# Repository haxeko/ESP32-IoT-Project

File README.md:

# ESP32-IoT-Project
Make ESP32 IoT Device

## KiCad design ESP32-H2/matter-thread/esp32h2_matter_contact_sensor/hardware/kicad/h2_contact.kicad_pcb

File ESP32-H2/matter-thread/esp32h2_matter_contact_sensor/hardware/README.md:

# h2-contact v1.0: PCB cảm biến cửa ESP32-H2 Matter over Thread

Bo mạch riêng cho firmware [`../`](../README.md): module **ESP32-H2-MINI-1-N4**, cấp nguồn và nạp qua **USB-C**, domino 2 chân cho **reed switch** (công tắc từ). Chân khớp với giá trị mặc định của firmware nên chỉ cần build và nạp, không phải đổi `menuconfig` (riêng LED phải bật, xem mục **Firmware**).

| | |
|---|---|
| Kích thước | 26 × 46 mm, bo góc R1,5; 2 lớp; FR-4 1,6 mm |
| Lắp ráp | toàn bộ SMD ở **mặt trên** (lắp 1 mặt); J2 (domino, xuyên lỗ) hàn tay |
| Luật thiết kế | dây ≥ 0,2 mm, khoảng cách ≥ 0,2 mm, via 0,6/0,3 mm, đồng cách mép bo ≥ 0,3 mm (trong khả năng tiêu chuẩn của JLCPCB) |
| Lỗ bắt vít | 2 × M2 (H1, H2) |
| Nguồn | USB-C 5 V → PTC 0,5 A → TVS SMF5.0A → AP2112K-3.3 (600 mA) |
| Nạp, log | USB-C (USB Serial/JTAG của ESP32-H2, GPIO26/27), USBLC6-2SC6 chống ESD; pad UART0 ở mặt dưới |

## Thư mục

| Đường dẫn | Nội dung |
|---|---|
| `kicad/` | Project KiCad 7 (`h2_contact.kicad_pro`): sơ đồ A3, PCB đã đi dây, symbol `ESP32-H2-MINI-1` và footprint module (thư viện Espressif) |
| `fab/h2_contact_gerbers.zip` | Gerber X2 + Excellon (lỗ oval của USB-C dạng G85) + drill map + job file: **file upload cho xưởng** |
| `fab/gerbers/` | các file trong zip, để xem từng lớp |
| `fab/h2_contact-BOM.csv` | BOM đầy đủ (có ghi chú linh kiện), kể cả J2 |
| `fab/h2_contact-BOM-JLCPCB.csv`, `fab/h2_contact-CPL-JLCPCB.csv` | BOM và file toạ độ (CPL) theo cột của JLCPCB, không có J2 (hàn tay) |
| `fab/h2_contact-pos.csv` | file toạ độ gốc của KiCad (mm, cả hai mặt) |
| `fab/h2_contact_schematic.pdf` | sơ đồ nguyên lý |
| `docs/images/` | ảnh mặt trên, lớp đồng trên, lớp đồng dưới (nhìn từ dưới) |
| `tools/gen/` | script dựng lại toàn bộ (mục **Dựng lại**) |

## Sơ đồ khối và gán chân

| Khối | Linh kiện | Chân ESP32-H2 (pad module) | Firmware (`menuconfig`) |
|---|---|---|---|
| Reed switch | J2 (REED, GND) → R7 10k kéo lên 3V3 ở phía domino → R8 1k → GPIO4; C7 100 nF xuống GND; D2 ESD 3,3 V | GPIO4 (18) | `CONTACT_SENSOR_GPIO=4`, `CONTACT_ACTIVE_LOW=y` (mặc định) |
| Nút BOOT / factory reset | SW2 xuống GND, R4 10k kéo lên | GPIO9 (23) | `FACTORY_RESET_GPIO=9`, giữ 6 s (mặc định) |
| Nút RESET | SW1 xuống GND; EN: R3 10k + C6 1 µF | EN (8) | — |
| Strapping | R5 10k kéo GPIO8 lên: cần cho chế độ nạp (GPIO8 = 1, GPIO9 = 0) | GPIO8 (22) | — |
| LED trạng thái | GPIO5 → R6 1k → LED xanh lá → GND (sáng mức cao) | GPIO5 (19) | `STATUS_LED_ENABLE=y`, `STATUS_LED_GPIO=5`, `STATUS_LED_ACTIVE_HIGH=y` |
| USB | J1 D−/D+ → U3 USBLC6-2SC6 → R10/R9 22 Ω → GPIO26/GPIO27 | 26, 27 | USB Serial/JTAG (nạp, log) |
| UART0 | pad TX0/RX0 (mặt dưới) | TXD0 (31), RXD0 (30) | log UART0 (mặc định của ESP-IDF) |
| Nguồn module | C4 10 µF + C5 100 nF sát chân 3V3 | 3V3 (3) | — |

- **VBAT (chân 15)** để trống: datasheet ESP32-H2-MINI-1 v1.6 (bảng 3, hình 7) ghi chân này nối sẵn với 3V3 bên trong module qua R2 0 Ω.
- Chân NC của module (4, 7, 17, 28, 29, 32–35) và GPIO không dùng (IO0–IO3, IO10–IO14, IO22, IO25) để trống. IO25 là chân strapping JTAG, để trống là mặc định.
- Mọi pad GND của module, kể cả EPAD, nối vào mặt GND phía trên; 2 mặt GND nối nhau bằng 70 via khâu và via của linh kiện.

## Nối reed switch

Domino J2, nhìn từ mép dưới của bo: trái **REED** (pad vuông), phải **GND**. Đưa 2 dây của reed switch vào hai chân, không phân cực.

- Dùng loại tiếp điểm **đóng khi nam châm ở gần** (cửa đóng → mạch kín). Đó là reed switch thường hở (NO) và cũng là kiểu cảm biến cửa có dây phổ biến (MC-38 và tương tự, thường được bán với tên "NC" theo cách gọi của ngành báo động: mạch kín khi cửa đóng). Firmware mặc định hiểu: **mạch kín = cửa đóng**. Loại ngược lại thì tắt `CONTACT_ACTIVE_LOW`.
- Dây dài được: R7 10k kéo lên ở phía domino cho dòng khoảng 0,3 mA qua tiếp điểm khi đóng; R8 1k + C7 100 nF lọc nhiễu; D2 chặn ESD. Firmware còn lọc dội 50 ms.
- Không nối nguồn ngoài vào J2.

## Firmware

Dùng nguyên firmware ở thư mục cha. Build như README firmware; muốn dùng LED trên bo thì bật một lựa chọn:

```bash
idf.py menuconfig   # Status LED → Status LED on a GPIO = y (GPIO5 và "LED lights when HIGH" đã đúng mặc định)
```

Nạp qua cổng USB-C của bo (Linux `/dev/ttyACM0`):

```bash
idf.py -p /dev/ttyACM0 flash monitor
```

Nếu USB không nhận (firmware lỗi): giữ **BOOT**, bấm **RESET**, nhả BOOT → chế độ nạp ROM. Sau khi firmware chạy, giữ **BOOT 6 giây** = factory reset Matter (cảnh báo: giữ BOOT **trong lúc cắm USB/reset** là vào chế độ nạp, không phải factory reset).

## Đặt làm ở JLCPCB (hoặc xưởng khác)

1. **PCB:** upload `fab/h2_contact_gerbers.zip`. 2 lớp, 1,6 mm, tuỳ chọn mặc định. Kích thước xưởng đọc được: 26 × 46 mm.
2. **Lắp ráp (PCBA):** chọn lắp **mặt trên** (Top). Upload `fab/h2_contact-BOM-JLCPCB.csv` và `fab/h2_contact-CPL-JLCPCB.csv`.
   - Cột **LCSC Part #** để trống: chọn mã trên trang JLC theo cột *Part / note* của `fab/h2_contact-BOM.csv` (giá trị, kích thước, điện áp). Chọn đúng **ESP32-H2-MINI-1-N4** (4 MB, anten PCB; không phải MINI-1U), **HRO TYPE-C-31-M-12** (USB-C 16 chân), **XKB TS-1187A** hoặc nút 5,1 × 5,1 mm cùng footprint.
   - Trong màn hình xem trước, **kiểm tra hướng xoay** từng linh kiện: quy ước góc của KiCad và JLC khác nhau ở một số footprint, hay gặp với U1, U2, U3 (SOT-23), J1 (USB-C), D1/D3 (cực tính). Chấm cực/chân 1: U1 chân 1 ở góc trên trái hàng pad (góc vát trên lớp Fab), U2/U3 dấu tam giác trên silkscreen cạnh chân 1, D1 vạch cathode ở phía +5V, D3 cathode nối GND.
3. **J2** (domino 3,5 mm 2 chân, ví dụ KF350-3.5-2P / Phoenix PT 1,5/2-3,5-H): hàn tay, hoặc thêm vào đơn lắp xuyên lỗ của JLC.
4. Mặt dưới chỉ có pad test (3V3, GND, TX0, RX0) và nhãn, không có linh kiện.

## Ghi chú thiết kế

- **Anten:** module đặt sát mép trên, đầu anten ra mép bo như Espressif khuyên. Vùng anten (5,4 mm trên cùng, cả bề ngang bo) không có đồng, dây hay via ở cả 2 lớp; dọc mép vùng này có một hàng via GND dày. Khi lắp vỏ: không để kim loại trong khoảng 15 mm quanh anten.
- **Dưới module:** lớp trên không có dây tín hiệu giữa các hàng pad (GND liền dưới module).
- **USB-C:** 16 chân có dữ liệu USB 2.0; CC1/CC2 mỗi chân 5,1k xuống GND (thiết bị nhận 5 V). D−/D+ xen kẽ trên đầu nối (B7 A6 A7 B6) nên phần thoát dây được đi tay và khoá: D− nối ở lớp trên, D+ đổi lớp qua 2 via; 2 chân VBUS nối nhau bằng cầu ở lớp dưới, dưới thân đầu nối.
- **Cặp D+/D−** không đi thành cặp vi sai 90 Ω (bo 2 lớp 1,6 mm, đường ngắn khoảng 25 mm, mỗi dây một phần ở lớp khác). Đủ cho USB Full-Speed 12 Mbit/s dùng để nạp và xem log; cảm biến chạy bình thường mà không cần USB dữ liệu.
- **Nguồn:** Espressif khuyên nguồn 3,3 V ≥ 350 mA; AP2112K-3.3 cho 600 mA. Tụ 10 µF ở đầu vào 5 V và ở chân 3V3 module như hướng dẫn thiết kế của Espressif.

## Trạng thái kiểm tra

Đã làm (KiCad 7.0.11, Freerouting 2.1.0):

- **DRC** (API pcbnew, sau khi đổ đồng): **0 vi phạm, 0 kết nối thiếu**, 0 lỗi footprint. Các mục tắt có chủ đích: silkscreen đè đồng/chồng nhau, silkscreen của module ("Antenna Area") sát mép bo, cảnh báo khác thư viện footprint.
- **Sơ đồ ↔ PCB:** netlist xuất từ sơ đồ (`kicad-cli`) so với net của từng pad trên PCB: **109/109 pad khớp** (`tools/gen/check_netlist.py`); H1/H2 chỉ có trên PCB.
- Footprint và bảng chân module lấy từ thư viện KiCad chính thức của Espressif (commit `dd76561`), đối chiếu datasheet ESP32-H2-MINI-1 v1.6.

**Chưa làm:**

- **ERC** chưa chạy: `kicad-cli` 7 không có ERC. Mở sơ đồ trong KiCad và chạy *Inspect → Electrical Rules Checker* trước khi đặt.
- Chưa sản xuất, chưa lắp, chưa đo trên bo thật; chưa có ảnh render 3D.
- Footprint USB-C, nút bấm, domino là footprint chuẩn của KiCad: so lại với datasheet của đúng mã linh kiện bạn chọn (nhất là khi đổi nhà sản xuất).

## Dựng lại

Toàn bộ project sinh ra từ `tools/gen/design.py` (linh kiện, vị trí, net). Cần KiCad 7.0.x (python `pcbnew`, `kicad-cli`), Java 21 và [Freerouting 2.1.0](https://github.com/freerouting/freerouting/releases/tag/v2.1.0); ảnh cần Node.js + Playwright Chromium.

```bash
cd tools/gen
FREEROUTING=/path/to/freerouting-2.1.0.jar ./route_all.sh   # symbol, PCB, thoát dây USB-C, Freerouting, via khâu, DRC
python3 build_sch.py         # sơ đồ (KiCad 7), UUID symbol = path footprint: "Update PCB from Schematic" khớp 1:1
python3 check_netlist.py     # sơ đồ ↔ PCB
python3 export_fab.py        # fab/ và docs/images/
```

Freerouting không cho kết quả giống hệt mỗi lần chạy: dây trong `kicad/` là bản đã kiểm tra ở trên.

## Giấy phép thư viện

Footprint `kicad/h2_contact.pretty/ESP32-H2-MINI-1.kicad_mod` lấy nguyên từ [espressif/kicad-libraries](https://github.com/espressif/kicad-libraries) (CC-BY-SA 4.0, kèm ngoại lệ giống thư viện KiCad: thiết kế dùng thư viện không bị ràng buộc bởi giấy phép này). Symbol `ESP32-H2-MINI-1` trong `kicad/h2_contact.kicad_sym` vẽ lại ở định dạng KiCad 7 theo số chân và tên chân của thư viện đó.

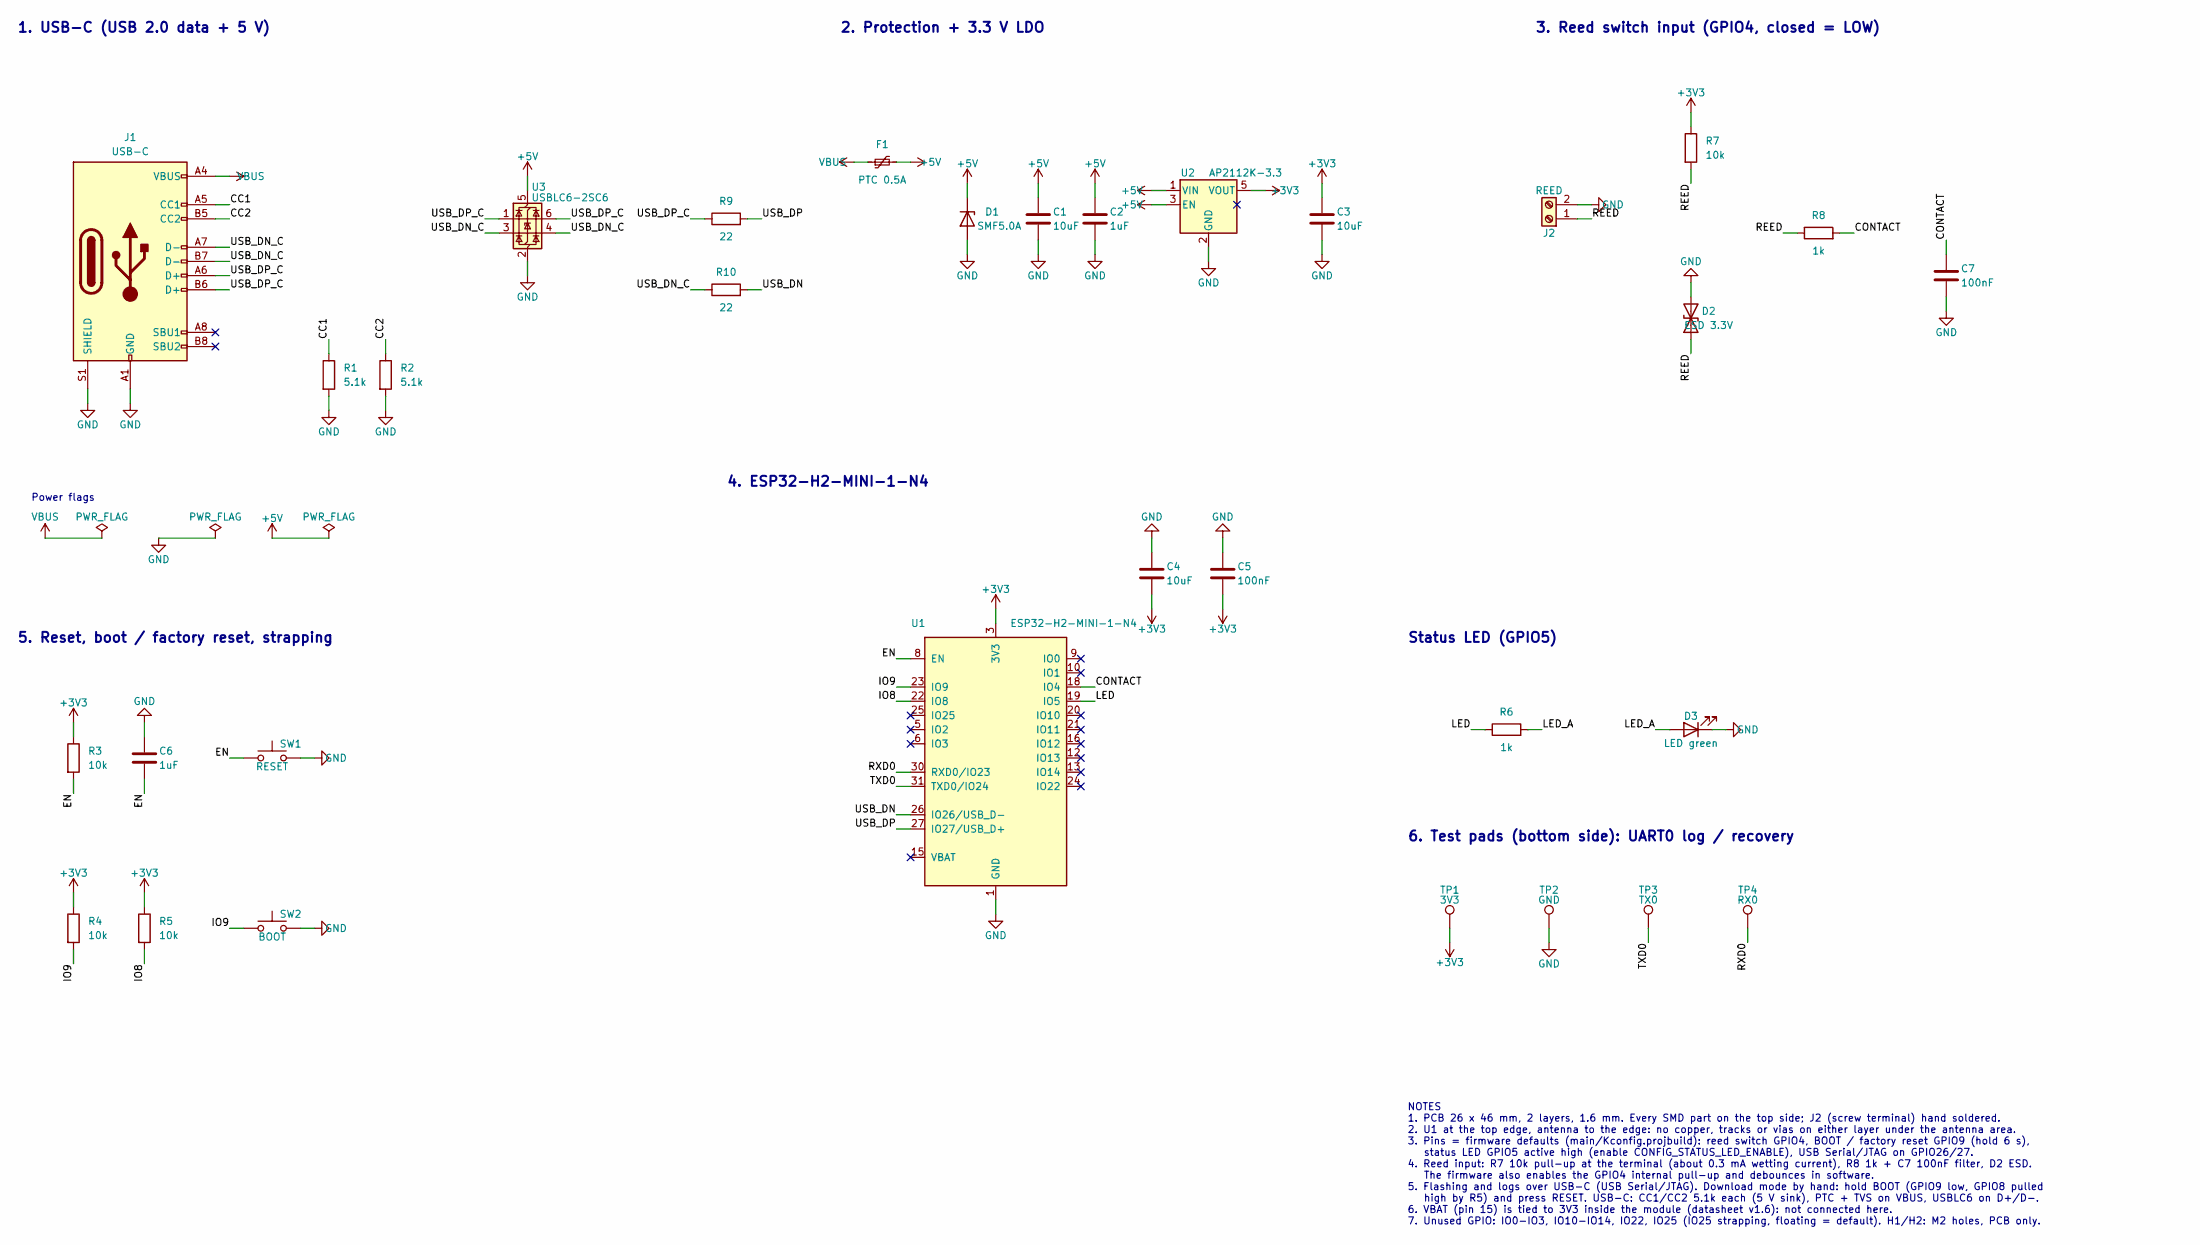
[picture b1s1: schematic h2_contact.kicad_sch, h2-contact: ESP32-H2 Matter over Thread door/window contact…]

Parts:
C1, C3, C4: 10uF; C_0805_2012Metric
C2, C6: 1uF; C_0603_1608Metric
C5, C7: 100nF; C_0603_1608Metric
D1: SMF5.0A; D_SOD-123F
D2: ESD 3.3V; D_SOD-323
D3: LED green; LED_0603_1608Metric
F1: PTC 0.5A; Fuse_1206_3216Metric
J1: USB-C; USB_C_Receptacle_HRO_TYPE-C-31-M-12
J2: REED; TerminalBlock_Phoenix_PT-1,5-2-3.5-H_1x02_P3.50mm_Horizontal
R1, R2: 5.1k; R_0603_1608Metric
R3, R4, R5, R7: 10k; R_0603_1608Metric
R6, R8: 1k; R_0603_1608Metric
R9, R10: 22; R_0603_1608Metric
SW1: RESET; SW_Push_1P1T_XKB_TS-1187A
SW2: BOOT; SW_Push_1P1T_XKB_TS-1187A
TP1: 3V3; TestPoint_Pad_D1.5mm
TP2: GND; TestPoint_Pad_D1.5mm
TP3: TX0; TestPoint_Pad_D1.5mm
TP4: RX0; TestPoint_Pad_D1.5mm
U1: ESP32-H2-MINI-1-N4; ESP32-H2-MINI-1
U2: AP2112K-3.3; SOT-23-5
U3: USBLC6-2SC6; SOT-23-6

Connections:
+3V3: C3.1, C4.2, C5.2, R3.1, R4.1, R5.1, R7.1, TP1.1, U1.3 (3V3), U2.5 (VOUT)
+5V: C1.1, C2.1, D1.1 (K), F1.2, U2.1 (VIN), U2.3 (EN), U3.5 (VBUS)
CC1: J1.A5 (CC1), R1.1
CC2: J1.B5 (CC2), R2.1
CONTACT: C7.1, R8.2, U1.18 (IO4)
EN: C6.2, R3.2, SW1.1, U1.8 (EN)
GND: C1.2, C2.2, C3.2, C4.1, C5.1, C6.1, C7.2, D1.2 (A), D2.2 (A2), D3.1 (K), J1.A1 (GND), J1.A12 (GND), J1.B1 (GND), J1.B12 (GND), J1.S1 (SHIELD), J2.2, R1.2, R2.2, SW1.2, SW2.2, TP2.1, U1.1 (GND), U1.2 (GND), U1.11 (GND), U1.14 (GND), U1.36 (GND), U1.37 (GND), U1.38 (GND), U1.39 (GND), U1.40 (GND), U1.41 (GND), U1.42 (GND), U1.43 (GND), U1.44 (GND), U1.45 (GND), U1.46 (GND), U1.47 (GND), U1.48 (GND), U1.49 (GND), U1.50 (GND), U1.51 (GND), U1.52 (GND), U1.53 (GND), U2.2 (GND), U3.2 (GND)
IO8: R5.2, U1.22 (IO8)
IO9: R4.2, SW2.1, U1.23 (IO9)
LED: R6.1, U1.19 (IO5)
LED_A: D3.2 (A), R6.2
REED: D2.1 (A1), J2.1, R7.2, R8.1
RXD0: TP4.1, U1.30 (RXD0/IO23)
TXD0: TP3.1, U1.31 (TXD0/IO24)
USB_DN: R10.2, U1.26 (IO26/USB_D-)
USB_DN_C: J1.A7 (D-), J1.B7 (D-), R10.1, U3.3 (I/O2), U3.4 (I/O2)
USB_DP: R9.2, U1.27 (IO27/USB_D+)
USB_DP_C: J1.A6 (D+), J1.B6 (D+), R9.1, U3.1 (I/O1), U3.6 (I/O1)
VBUS: F1.1, J1.A4 (VBUS), J1.A9 (VBUS), J1.B4 (VBUS), J1.B9 (VBUS)

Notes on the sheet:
1. USB-C (USB 2.0 data + 5 V)
Power flags
2. Protection + 3.3 V LDO
3. Reed switch input (GPIO4, closed = LOW)
4. ESP32-H2-MINI-1-N4
5. Reset, boot / factory reset, strapping
Status LED (GPIO5)
6. Test pads (bottom side): UART0 log / recovery
NOTES 1. PCB 26 x 46 mm, 2 layers, 1.6 mm. Every SMD part on the top side; J2 (screw terminal) hand soldered. 2. U1 at the top edge, antenna to the edge: no copper, tracks or vias on either layer under the antenna area. 3. Pins = firmware defaults (main/Kconfig.projbuild): reed switch GPIO4, BOOT /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

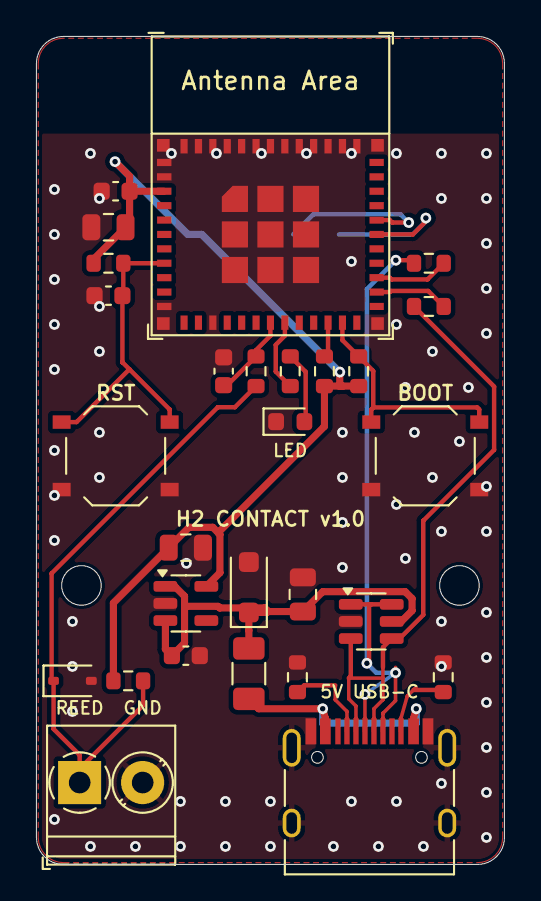
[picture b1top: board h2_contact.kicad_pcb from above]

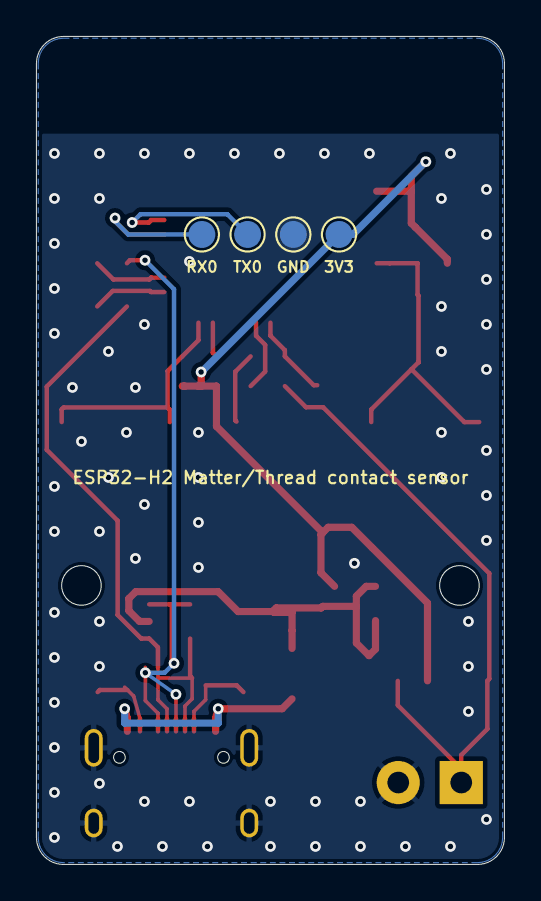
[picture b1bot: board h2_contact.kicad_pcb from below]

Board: 2 copper layers, 26.0 x 46.0 mm, 34 parts (4 on the bottom side), 19 nets.

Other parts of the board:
H1, H2: M2; MountingHole_2.2mm_M2

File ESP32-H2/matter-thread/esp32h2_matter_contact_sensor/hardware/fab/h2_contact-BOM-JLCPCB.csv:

Comment,Designator,Footprint,LCSC Part #
10uF,"C1,C3,C4",C_0805_2012Metric,
1uF,"C2,C6",C_0603_1608Metric,
100nF,"C5,C7",C_0603_1608Metric,
SMF5.0A,D1,D_SOD-123F,
ESD 3.3V,D2,D_SOD-323,
LED green,D3,LED_0603_1608Metric,
PTC 0.5A,F1,Fuse_1206_3216Metric,
USB-C,J1,USB_C_Receptacle_HRO_TYPE-C-31-M-12,
5.1k,"R1,R2",R_0603_1608Metric,
10k,"R3,R4,R5,R7",R_0603_1608Metric,
1k,"R6,R8",R_0603_1608Metric,
22,"R9,R10",R_0603_1608Metric,
RESET,SW1,SW_Push_1P1T_XKB_TS-1187A,
BOOT,SW2,SW_Push_1P1T_XKB_TS-1187A,
ESP32-H2-MINI-1-N4,U1,ESP32-H2-MINI-1,
AP2112K-3.3,U2,SOT-23-5,
USBLC6-2SC6,U3,SOT-23-6,

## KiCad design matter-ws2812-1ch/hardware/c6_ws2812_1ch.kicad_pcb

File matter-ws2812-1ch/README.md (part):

# matter-ws2812-1ch: bo điều khiển LED WS2812 1 kênh (ESP32-C6-MINI-1, nguồn 5–12 V)

Bo mạch KiCad 9 dùng module **ESP32-C6-MINI-1** để điều khiển một dải LED WS2812/WS2812B (5 V) hoặc WS2811/WS2815 (12 V). ESP32-C6 có Wi‑Fi 6, BLE 5 và radio IEEE 802.15.4, nên firmware viết sau có thể chạy **Matter over Wi‑Fi** hoặc **Matter over Thread**. Bo có:

- **1 ngõ ra LED** với cầu đấu `+ D −`.
- **1 nút** để vào chế độ kết nối và factory reset.
- **Công tắc gạt 3 nấc** để chọn số endpoint Matter: chia dải LED thành 1, 2 hoặc 3 đoạn, mỗi đoạn là một đèn riêng.
- **Header J7** đưa ra 1 GPIO trống (IO18) kèm 3V3 và GND.
- **6 pad nạp UART0** ở mặt dưới, và cổng USB‑C để nạp code/debug.

### Thay đổi ở r3.0

- Chỉ còn **1 ngõ ra LED** (J2). Bỏ 2 cầu đấu kênh 2/3.
- Header J7 còn **1 GPIO**: 1×3 chân `3V3 IO18 GND`.
- **Board còn 39 × 33 mm**, giảm khoảng 33 % diện tích so với r2.0 (48 × 40 mm) và khoảng 76 % so với r1.1 (84 × 63 mm).
- IC dịch mức đổi sang **74AHCT1G125** (1 cổng, SOT-23-5), điện trở 100 Ω rời.
- TVS nhỏ hơn: **SMF15A** (200 W). Tụ lọc VLED **47 µF 25 V** (5 × 5,4 mm).
- Cầu đấu, công tắc gạt và header J7 cùng nằm ở mép dưới. Module vẫn ở mép trên, anten chìa ra ngoài.
- Thư mục project đổi từ `matter-ws2812-3ch` thành `matter-ws2812-1ch`; file KiCad đổi tên thành `c6_ws2812_1ch.*`.

## Thông số

| Mục | Giá trị |
|---|---|
| Vi điều khiển | ESP32-C6-MINI-1-N4: Wi‑Fi 6 2,4 GHz, BLE 5, 802.15.4 (Thread/Zigbee), flash 4 MB |
| Nguồn vào | 5–12 V DC, cầu đấu 3,5 mm. Nguồn này cấp thẳng cho dải LED: dải 5 V cắm nguồn 5 V, dải 12 V cắm nguồn 12 V |
| Dòng | Tối đa **5 A**. Trên bo **không có cầu chì**: dùng nguồn có bảo vệ ngắn mạch (xem mục nguồn) |
| Bảo vệ | Chống cắm ngược bằng MOSFET P SiSS27DN (−30 V, tối đa 9 mΩ ở −4,5 V), TVS SMF15A, tụ lọc 47 µF |
| 3,3 V | Buck AP63203 (vào 3,8–32 V, 2 A) |
| Mức tín hiệu DATA | 5 V, qua 74AHCT1G125 và điện trở 100 Ω. IC này được cấp từ LDO AP7381‑5.0 lấy điện từ nguồn LED |
| USB-C | Nạp code và debug qua USB Serial/JTAG của C6 (IO12/IO13). Có chống ESD USBLC6-2SC6. USB chỉ nuôi phần logic, không bao giờ cấp điện cho dải LED |
| Giao diện | Nút LINK/RESET (GPIO9), LED xanh báo trạng thái (GPIO8), công tắc 3 nấc (GPIO21/22/23), header J7 (GPIO18), 6 pad UART0 ở mặt dưới |
| PCB | 39 × 33 mm, 2 lớp, dày 1,6 mm. Kể cả phần anten chìa ra: 39 × 38,3 mm |

## Cấu trúc thư mục

| Thư mục | Nội dung |
|---|---|
| `hardware/` | Project KiCad 9: `c6_ws2812_1ch.kicad_pro/.kicad_sch/.kicad_pcb`, thư viện footprint riêng `.pretty` (module C6 có via GND, pad nạp, USB‑C và công tắc gạt đã cắt silkscreen ở mép board), mô hình 3D dạng hộp trong `.3dshapes` |
| `fab/` | `c6_ws2812_1ch_gerbers.zip` để upload, thư mục `gerbers/`, BOM, file toạ độ (CPL), PDF sơ đồ |
| `docs/images/` | Ảnh render 3D, lớp đồng trên/dưới, sơ đồ nguyên lý |
| `tools/` | Script Python sinh toàn bộ project: `design.py` (linh kiện và net), `layout.py` (vị trí), `build_all.sh` |

## Sơ đồ nguyên lý

Bản đầy đủ ở `fab/c6_ws2812_1ch_schematic.pdf`. Sơ đồ có các khối sau:

1. **Nguồn vào:** J1 → Q1 (MOSFET P chống cắm ngược, D4 kẹp Vgs ở 15 V, R1 10k kéo gate xuống GND) → đường **VLED**. TVS D3 và C1 47 µF đặt trên VLED.
2. **Ngõ ra:** VLED nối thẳng vào chân `+` của J2.
3. **3,3 V:** VLED qua D1 và VBUS (USB) qua D2 cùng đổ vào V_SYS (hai diode Schottky B5819W). V_SYS vào buck AP63203 (L1 3,9 µH, tụ vào 10 µF và 100 nF, tụ ra 2 × 22 µF).
4. **5 V cho IC dịch mức:** LDO AP7381‑5.0 chịu được 40 V. Khi nguồn vào là 5 V, LDO ra khoảng 4,8–4,9 V (vẫn trong dải 4,5–5,5 V của 74AHCT1G125). Khi chỉ cắm USB, IC dịch mức không có điện, nên không có dòng chạy vào chân DATA của dải LED đang tắt. Ngõ vào họ AHCT chịu được 5,5 V cả khi IC không có điện.
5. **Dịch mức:** GPIO14 → 74AHCT1G125 (ngõ vào có R9 10k kéo xuống để LED không nhận rác khi ESP đang khởi động; chân OE nối GND) → R10 100 Ω → chân `D` của J2.
6. **ESP32-C6:** tụ 100 nF sát chân 3V3 (hai tụ 22 µF của buck nằm cách khoảng 4 mm), mạch RC 10k + 1 µF ở chân EN, R6 10k kéo IO8 lên.
7. **USB-C:** CC1/CC2 nối điện trở 5,1k xuống GND, D+/D− đi qua USBLC6-2SC6.
8. **Mở rộng:** J7 đưa ra `3V3, IO18, GND`.

## Gán chân

| GPIO | Chân module | Chức năng | Ghi chú |
|---|---|---|---|
| IO14 | 19 | DATA dải LED | Không có pull sau reset; R9 10k kéo xuống |
| IO9 | 23 | Nút LINK/RESET (cũng là BOOT) | Pull-up nội, nhấn = 0 |
| IO8 | 22 | LED trạng thái, 0 = sáng | Chân strap, R6 10k kéo lên |
| IO21 / IO22 / IO23 | 27 / 28 / 29 | Chân 1 / 2 / 4 của công tắc SW2 = nấc 1 / 2 / 3 | Chân 3 (chung) của SW2 nối GND |
| IO18 | 24 | J7 chân 2 | |
| IO12 / IO13 | 17 / 18 | USB D− / D+ | |
| RXD0 / TXD0 | 30 / 31 | UART0 RX / TX | Ra pad nạp |
| IO0–IO7, IO15, IO19, IO20 | | Để trống | |

Các chân strap của ESP32-C6 đều ở trạng thái an toàn khi khởi động:

- **IO9 = 1, IO8 = 1:** chạy firmware bình thường. Giữ nút (IO9 = 0) lúc reset thì vào chế độ nạp; lúc đó IO8 phải bằng 1, nên có R6 kéo lên. Mạch LED nối từ 3V3 qua R8 vào IO8, không kéo chân này xuống.
- **IO4/IO5 (MTMS/MTDI)** và **IO15** để trống. IO15 chỉ có tác dụng strap khi đã đốt eFuse JTAG (mặc định chưa đốt).

## Header J7: 1 GPIO tự do

| Chân J7 | Tín hiệu | Lưu ý |
|---|---|---|
| 1 | 3V3 | Lấy từ buck AP63203; nên dùng dưới khoảng 300 mA cho thiết bị ngoài |
| 2 | IO18 | GPIO thường |
| 3 | GND | |

- IO18 là chân SDIO của C6 (bo không dùng SDIO). Có pull-up yếu chỉ trong lúc reset; sau reset không có pull nào.
- Mức logic 3,3 V, **không chịu 5 V**. Nên dùng dưới khoảng 20 mA. Tải lớn hơn (relay, quạt, đèn) thì qua transistor/MOSFET.
- Dùng được làm ngõ vào nút bấm/cảm biến (ví dụ cảm biến chuyển động PIR, DS18B20), ngõ ra điều khiển relay qua transistor, PWM (LEDC), hoặc một dây 1-Wire.
- Header bước 2,54 mm ở mép dưới, giữa cầu đấu J2 và công tắc gạt. Chân 1 (3V3) là pad vuông, ở phía trên. Tên chân in ở mặt dưới (`J7: 3V3 IO18 GND`).

## Nút LINK/RESET (gợi ý cho firmware)

- **Nhấn nhanh:** bật/tắt đèn, hoặc mở lại cửa sổ kết nối Matter.
- **Giữ ≥ 5 giây rồi nhả:** factory reset, xoá Wi‑Fi/Thread và thông tin ghép nối.
- **Giữ nút trong lúc cắm điện:** ESP32‑C6 vào chế độ nạp ROM (GPIO9 = 0 khi reset). Dùng để cứu mạch khi firmware lỗi.

LED xanh (GPIO8) dùng để báo trạng thái, ví dụ: nháy chậm khi chờ kết nối, nháy nhanh khi đang giữ nút để reset, sáng một lúc khi kết nối xong.

## Công tắc gạt 3 nấc: số endpoint

Bo chỉ có một ngõ ra, nên công tắc dùng để **chia dải LED thành 1, 2 hoặc 3 đoạn**. Mỗi đoạn là một endpoint Matter (một đèn riêng trong app: bật/tắt, độ sáng, màu riêng). Ví dụ: một dải chạy quanh phòng chia thành 3 vùng. Số LED mỗi đoạn đặt trong firmware.

SW2 là **C&K PCM13SMTR**. Bảng "switch function" trong datasheet C&K: **nấc 1 nối chân 1‑3, nấc 2 nối 2‑3, nấc 3 nối 3‑4**, tức chân 3 là chân chung. Bo nối:

- **Chân 3** của SW2 nối GND.
- **Chân 1, 2, 4** vào **IO21, IO22, IO23**.

Firmware bật pull-up nội cho 3 GPIO rồi đọc: chân nào bằng 0 thì công tắc đang ở nấc tương ứng.

```c
#include "driver/gpio.h"
#include "esp_rom_sys.h"

/* SW2 chân 1, 2, 4 -> nấc 1, 2, 3 (chân 3 là chân chung, nối GND) */
static const gpio_num_t EP_PIN[3] = {GPIO_NUM_21, GPIO_NUM_22, GPIO_NUM_23};

/* Trả về 1, 2 hoặc 3 endpoint; 0 nếu công tắc đang nằm giữa hai nấc */
int read_endpoint_switch(void)
{
    gpio_config_t io = {
        .pin_bit_mask = (1ULL << GPIO_NUM_21) | (1ULL << GPIO_NUM_22) | (1ULL << GPIO_NUM_23),
        .mode = GPIO_MODE_INPUT,
        .pull_up_en = GPIO_PULLUP_ENABLE,
    };
    gpio_config(&io);
    esp_rom_delay_us(50);
    for (int i = 0; i < 3; i++) {
        if (gpio_get_level(EP_PIN[i]) == 0) {
            return i + 1;
        }
    }
    return 0;
}
```

- Nên đọc công tắc **một lần lúc khởi động**. Danh sách endpoint là một phần của thiết bị đã ghép nối Matter. Nên khi số endpoint đổi so với lần trước (lưu trong NVS), firmware nên yêu cầu factory reset và ghép lại thay vì đổi ngầm.
- Công tắc nằm ở mép dưới, góc phải. Vạch `1 2 3` in phía trên công tắc: gạt sang trái (về phía J7) là nấc 1, gạt sang phải là nấc 3.
- Cần gạt nhô ra khoảng 0,75 mm khỏi mép dưới board, đủ để gạt bằng móng tay hoặc đầu bút.
- Nếu không cần chia đoạn, chỉ cần để công tắc ở nấc 1. Muốn bo nhỏ hơn nữa thì có thể bỏ hẳn công tắc trong bản sau.

## Gợi ý cho firmware

- Một dải LED chỉ cần **1 kênh RMT TX** (`led_strip` backend RMT).
- Firmware `ESP32-C3/matter-wifi/matter-rgb-light-ws2812` trong repo có thể dùng cho bo này ở chế độ 1 endpoint: `idf.py set-target esp32c6`, đặt `CONFIG_LED_GPIO=14`, giữ `CONFIG_APP_BUTTON_GPIO=9`. Chưa build thử cho C6.
- Với Matter over Thread, cần một Thread Border Router trong nhà (ví dụ HomePod mini, Apple TV 4K, Google Nest Hub 2, hoặc OTBR tự dựng).

## Nguồn và dòng

- **Chọn nguồn theo dải LED:** WS2812/WS2812B cần 5 V, WS2811/WS2815 loại 12 V cần 12 V. Mức DATA luôn là 5 V, hợp với cả hai loại.
- **Không có cầu chì trên bo.** Nếu dây ra dải LED bị chập, dòng chỉ bị giới hạn bởi nguồn. Nên dùng nguồn có bảo vệ ngắn mạch (phần lớn nguồn tổ ong có, nhưng nên xem thông số của nguồn). Với nguồn lớn hoặc dây ra mảnh, nên gắn cầu chì trên dây.
- **Tụ ở đầu dải LED:** C1 trên bo chỉ 47 µF. Nên gắn thêm tụ 470–1000 µF ngay đầu vào dải LED, như khuyến cáo thông thường cho WS2812.
- **Đường đồng:** VIN và VLED là vùng đồng rộng khoảng 3,5–4 mm ở lớp trên (J1 → Q1 → chân `+` của J2). GND là mặt đồng liền ở lớp dưới. Theo ước tính IPC‑2221 với đồng 1 oz, đường VLED nóng thêm khoảng 7 °C khi chạy 5 A.
- **Tổn hao Q1:** SiSS27DN tối đa 9 mΩ ở Vgs = −4,5 V, nên ở 5 A chỉ khoảng 0,25 W.
- **Cầu đấu 3,5 mm:** loại phổ biến (KF350, Phoenix PT 1,5) chịu khoảng 8–10 A mỗi chân; xem datasheet loại mua được. Dây 0,5–1,5 mm².
- **Dải LED dài:** cấp nguồn thêm ở giữa hoặc ở cuối dải (power injection) trực tiếp từ nguồn. Không kéo toàn bộ dòng qua bo.
- **Cắm USB khi đã có nguồn LED:** an toàn. Diode D1/D2 chọn nguồn cao hơn cho phần logic, và USB không bao giờ nối vào VLED.

## Bố trí PCB

| Lớp trên | Lớp dưới |
|---|---|
|  |  |

- **Mép trên:** USB‑C (góc trái), buck 3,3 V, rồi module ESP32-C6. Mép trên của board trùng chỗ bắt đầu vùng anten của module, nên toàn bộ anten nằm ngoài board, không có đồng bên dưới. Khi làm hộp, không đặt kim loại hoặc dây điện sát phần anten.
- **Mép dưới:** cầu đấu nguồn J1, cầu đấu LED J2, header J7, công tắc gạt SW2. Mọi dây nối đều đi ra một phía.
- **Đường công suất:** đi theo vùng đồng, không dùng đường mảnh: J1 → Q1 → vùng VLED → chân `+` của J2. Chân cầu đấu và Q1 nối đặc vào vùng đồng (không dùng thermal relief).
- **Đường DATA:** từ IO14 qua 74AHCT1G125 (nằm phía trên cầu đấu J2) và R10 xuống chân `D`. Đoạn sau R10 đi thẳng ở lớp trên; hai đoạn ngắn trước đó chui xuống lớp dưới để băng qua đường nguồn.
- **GND:** mặt GND lớp dưới gần như liền. 4 via trong pad giữa của module, 11 via khâu và các via cạnh chân GND nối mảng GND lớp trên xuống lớp dưới.
- **Pad nạp UART0:** 6 pad Ø1,5 mm, bước 2,54 mm, ở **mặt dưới, dưới thân module** (`3V3 EN GND IO9 RX0 TX0`). Tên từng pad in ở mặt dưới; nhìn từ mặt dưới, thứ tự từ trái sang phải là TX0 → 3V3.

## Nạp firmware

1. **Qua USB-C (khuyên dùng):** cắm cáp, chạy `idf.py -p /dev/ttyACM0 flash monitor`. Chip mới hoặc firmware treo: giữ nút LINK/RESET rồi mới cắm cáp.
2. **Qua pad UART0:** dùng mạch USB‑UART 3,3 V nối vào pad mặt dưới (TX0 → RX, RX0 → TX, chung GND). Có thể dùng kim pogo hoặc hàn tạm dây. Nối IO9 với GND, chạm EN xuống GND rồi nạp.
3. Không cần nguồn LED khi nạp; USB tự nuôi phần logic. Khi nạp qua pad UART, cấp 3,3 V vào pad `3V3` hoặc cắm USB‑C, không cấp cả hai cùng lúc.

## Đặt làm mạch

- Upload `fab/c6_ws2812_1ch_gerbers.zip`: 2 lớp, 1,6 mm, đồng 1 oz.
- Luật dùng: đường tối thiểu 0,25 mm, khoảng hở tối thiểu 0,2 mm (VIN/VLED 0,25 mm), via 0,6/0,3 mm, đồng cách mép board 0,4 mm. Đều nằm trong khả năng tiêu chuẩn của JLCPCB/PCBWay.
- Lắp ráp SMT: dùng `fab/c6_ws2812_1ch-BOM.csv` và `fab/c6_ws2812_1ch-pos.csv`. Gốc toạ độ là góc dưới trái board. Một số linh kiện có thể bị lệch góc xoay trong trình xem của nhà mạch; kiểm tra lại ở bước preview.
- Linh kiện cắm (cột `Mount = THT`: 2 cầu đấu, header J7) hàn tay sau. Nút và công tắc gạt đều là linh kiện dán.
- Cột LCSC có mã cho các linh kiện đã đối chiếu: AP63203WU‑7 C780769, USBLC6‑2SC6 C7519, HRO TYPE‑C‑31‑M‑12 C165948, B5819W C8598, C&K PCM13SMTR C221842, XKB TS‑1187A C318884, LED xanh C72043, và các điện trở/tụ 0603 loại basic thông dụng. Các dòng còn trống thì chọn theo MPN.
- Bo dày đặc nên nhiều ký hiệu linh kiện (khối buck U2/L1/C3–C6, Q1, D1–D3, R1–R4, U3, …) không in được trên silkscreen; vị trí đầy đủ có trong file CPL và lớp Fab của PCB.

## Cần kiểm tra trước khi đặt

1. **Công tắc gạt SW2:** footprint `SW_SP3T_PCM13` của KiCad khớp bản vẽ "PC mounting" trong datasheet C&K (4 chân, cách nhau 1,5 / 3,0 / 1,5 mm). Kiểu nối 1‑3 / 2‑3 / 3‑4 lấy từ bảng "switch function" của datasheet. Nếu firmware đọc ra nấc bị đảo chiều, chỉ cần đảo bảng tra.
2. **Q1:** SiSS27DN (Vishay). Nếu thay, chọn MOSFET P vỏ PowerPAK 1212‑8 cùng sơ đồ chân (1–3 S, 4 G, pad lớn D), VDS ≥ 20 V, VGS ±20 V, RDS(on) ≤ 10 mΩ ở −4,5 V.
3. **Cầu đấu:** footprint Phoenix PT 1,5/x‑3,5‑H (lỗ 1,2 mm, bước 3,5 mm), lỗ luồn dây quay ra mép dưới board. Loại KF350‑3.5 phổ biến có cùng bước chân.
4. **Module ESP:** footprint ESP32‑C6‑MINI‑1 của KiCad, thêm 4 via GND 0,3 mm (phủ mask) ở khe giữa các ô của pad giữa. Vùng cấm đồng của anten thu hẹp còn ±12 mm quanh module và nằm hẳn ngoài board. Các chân GND quanh module nối qua mảng GND lớp trên dưới bụng module; riêng pad góc 51 (kẹp giữa IO18 và IO19) có đường đi riêng.
5. **Mô hình 3D:** thư viện 3D của KiCad 9.0.9 chưa có mô hình cho module C6, USB‑C HRO, nút TS‑1187A và MOSFET PowerPAK. Script sinh hộp đơn giản thay thế (`hardware/c6_ws2812_1ch.3dshapes`), chỉ để xem render.

## Trạng thái kiểm tra

- **ERC (KiCad 9.0.9):** 0 lỗi, 0 cảnh báo.
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
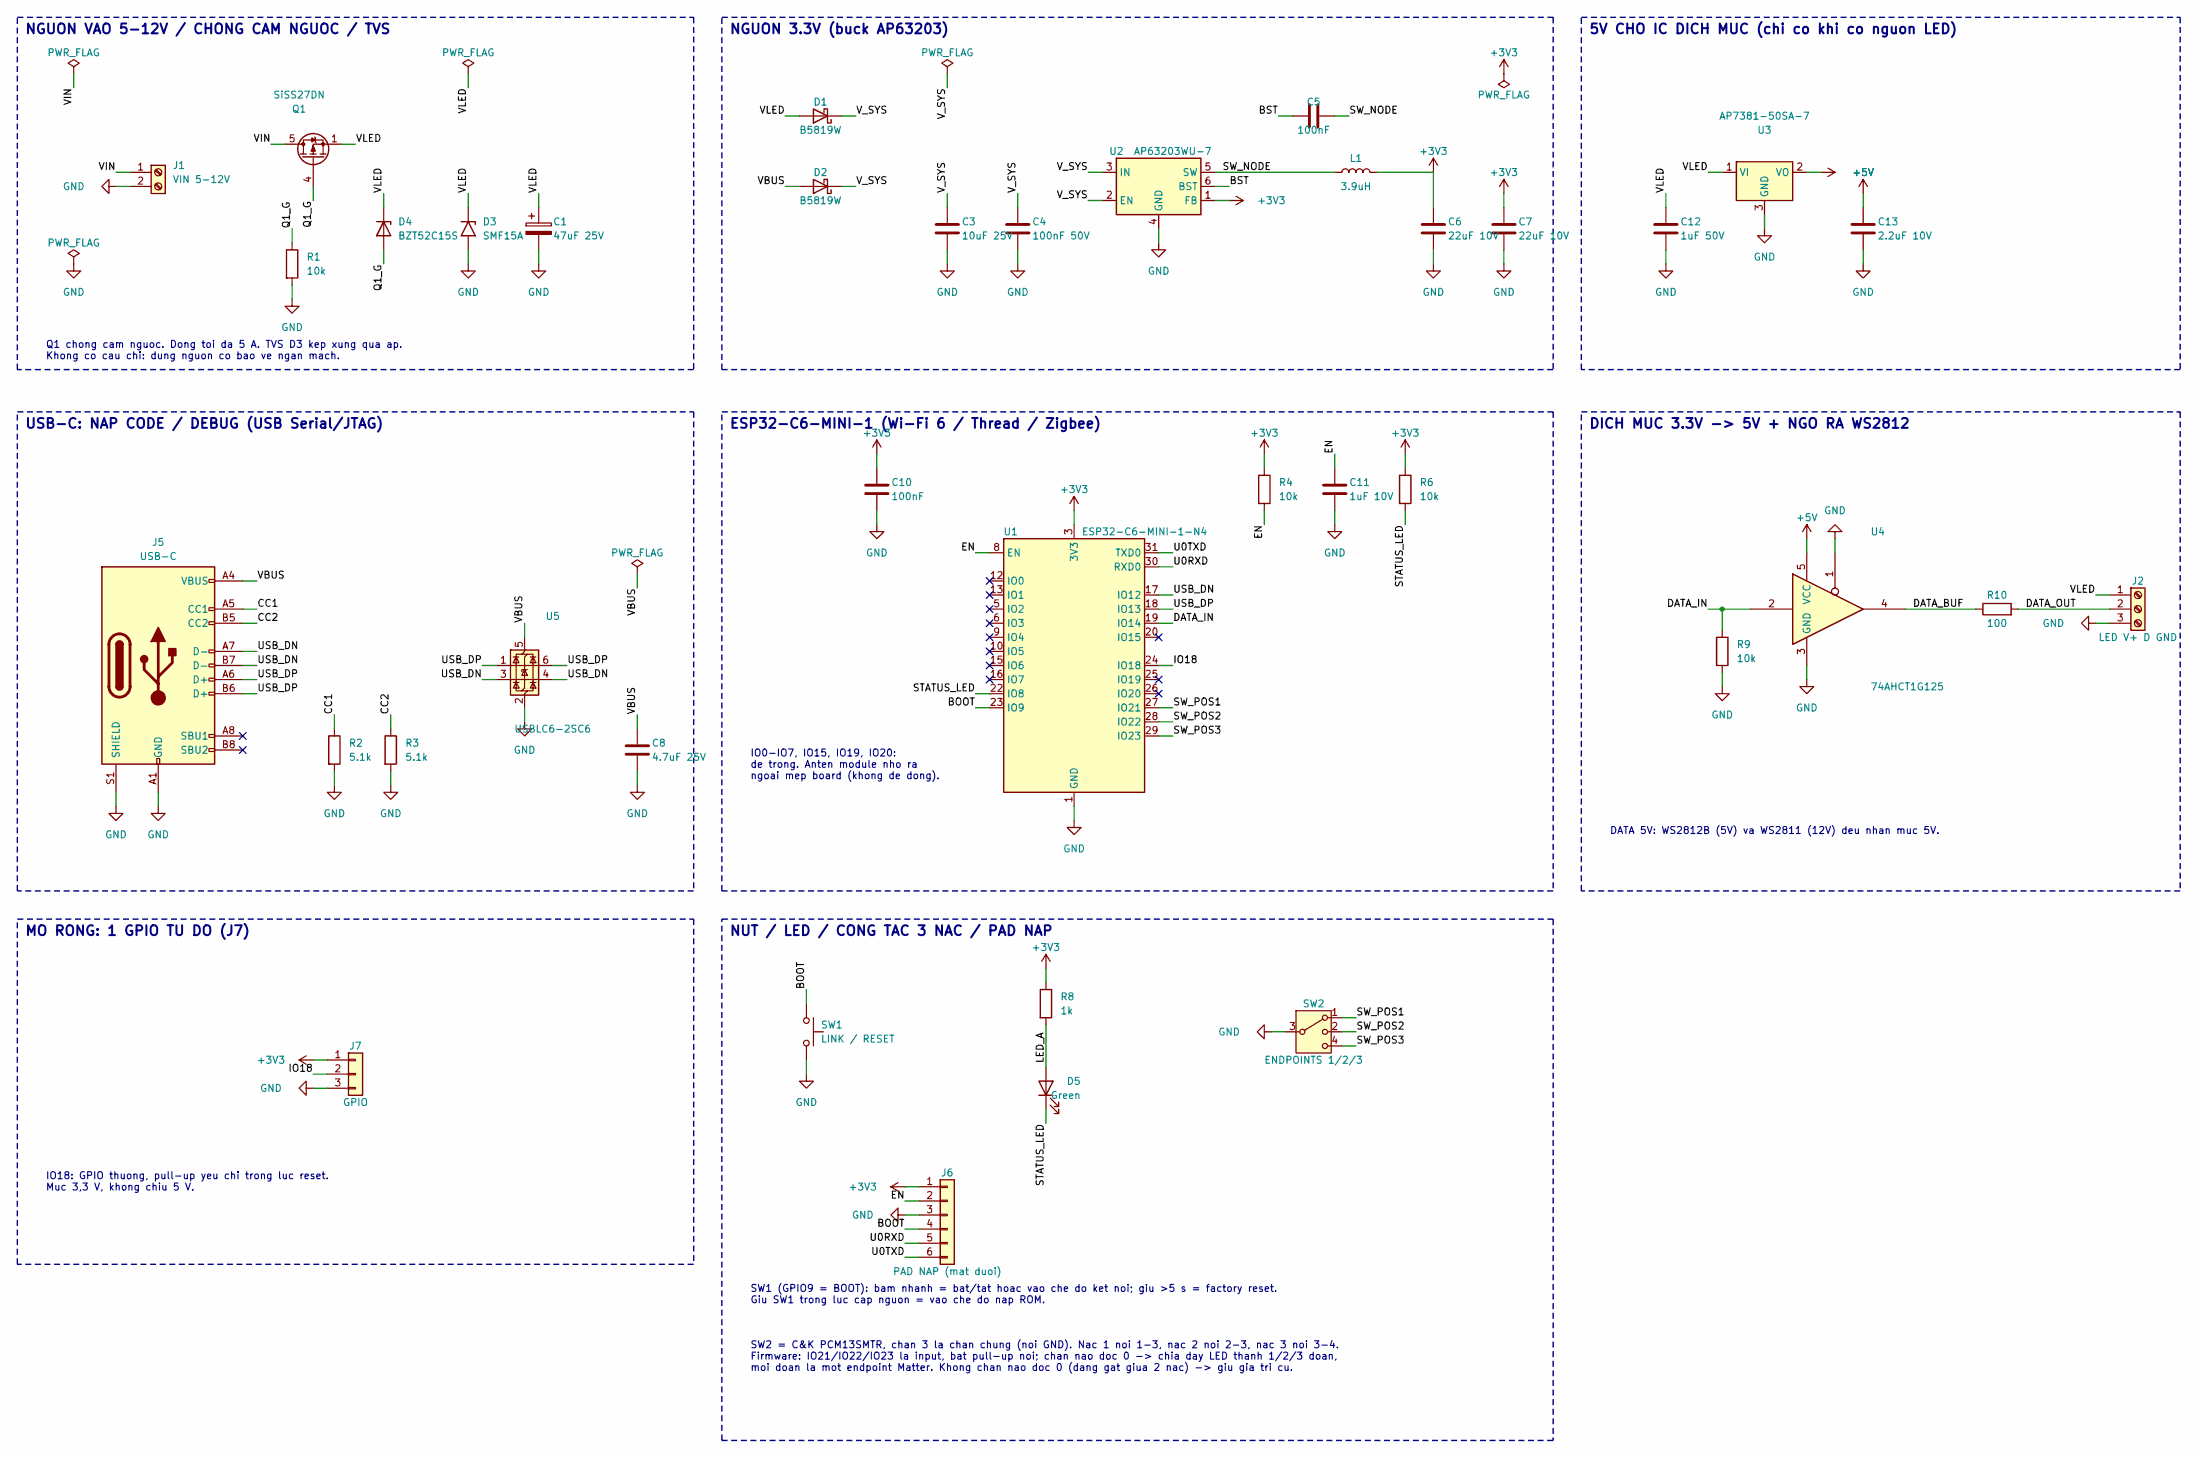
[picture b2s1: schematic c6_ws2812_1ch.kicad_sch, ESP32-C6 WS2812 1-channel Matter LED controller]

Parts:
C1: 47uF 25V; CP_Elec_5x5.4; MPN 47uF 25V 5x5.4 SMD electrolytic
C3: 10uF 25V; C_0805_2012Metric; MPN MLCC 10uF 25V
C4: 100nF 50V; C_0603_1608Metric; MPN MLCC 100nF 50V; LCSC C14663
C5, C10: 100nF; C_0603_1608Metric; MPN MLCC 100nF; LCSC C14663
C6, C7: 22uF 10V; C_0805_2012Metric; MPN MLCC 22uF 10V
C8: 4.7uF 25V; C_0805_2012Metric; MPN MLCC 4.7uF 25V
C11: 1uF 10V; C_0603_1608Metric; MPN MLCC 1uF 10V
C12: 1uF 50V; C_0805_2012Metric; MPN MLCC 1uF 50V
C13: 2.2uF 10V; C_0603_1608Metric; MPN MLCC 2.2uF 10V
D1, D2: B5819W; D_SOD-123; MPN B5819W; LCSC C8598
D3: SMF15A; D_SMF; MPN SMF15A
D4: BZT52C15S; D_SOD-323; MPN BZT52C15S
D5: Green; LED_0603_1608Metric; MPN LED 0603 green; LCSC C72043
J1: VIN 5-12V; TerminalBlock_Phoenix_PT-1,5-2-3.5-H_1x02_P3.50mm_Horizontal; MPN Terminal block 2P 3.5mm (Phoenix PT 1,5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
J2: LED V+ D GND; TerminalBlock_Phoenix_PT-1,5-3-3.5-H_1x03_P3.50mm_Horizontal; MPN Terminal block 3P 3.5mm (Phoenix PT 1,5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
J5: USB-C; USB_C_Receptacle_HRO_TYPE-C-31-M-12_EdgeSilk; MPN HRO TYPE-C-31-M-12; LCSC C165948
J6: PAD NAP (mat duoi); ProgPads_1x06_P2.54mm_D1.5mm_SMD; MPN (pads on the bottom side, nothing to mo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
J7: GPIO; PinHeader_1x03_P2.54mm_Vertical; MPN Pin header 1x3 2.54mm
L1: 3.9uH; L_Sunlord_SWPA3015S; MPN SWPA3015S3R9MT
Q1: SiSS27DN; Vishay_PowerPAK_1212-8_Single; MPN SiSS27DN-T1-GE3
R1, R4, R6, R9: 10k; R_0603_1608Metric; MPN 0603 1% 10k; LCSC C25804
R2, R3: 5.1k; R_0603_1608Metric; MPN 0603 1% 5.1k; LCSC C23186
R8: 1k; R_0603_1608Metric; MPN 0603 1% 1k; LCSC C21190
R10: 100; R_0603_1608Metric; MPN 0603 1% 100; LCSC C22775
SW1: LINK / RESET; SW_Push_1P1T_XKB_TS-1187A; MPN XKB TS-1187A-B-A-B; LCSC C318884
SW2: ENDPOINTS 1/2/3; SW_SP3T_PCM13_EdgeSilk; MPN C&K PCM13SMTR (SP3T, pos.1 = 1-3, pos.2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; LCSC C221842
U1: ESP32-C6-MINI-1-N4; ESP32-C6-MINI-1_ThermalVias; MPN ESP32-C6-MINI-1-N4
U2: AP63203WU-7; TSOT-23-6; MPN AP63203WU-7; LCSC C780769
U3: AP7381-50SA-7; SOT-23; MPN AP7381-50SA-7
U4: 74AHCT1G125; SOT-23-5; MPN SN74AHCT1G125DBVR
U5: USBLC6-2SC6; SOT-23-6; MPN USBLC6-2SC6; LCSC C7519

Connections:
+3V3: C6.1, C7.1, C10.1, J6.1, J7.1, L1.2, R4.1, R6.1, R8.1, U1.3 (3V3), U2.1 (FB)
+5V: C13.1, U3.2 (VO), U4.5 (VCC)
/BOOT: J6.4, SW1.1, U1.23 (IO9)
/BST: C5.1, U2.6 (BST)
/CC1: J5.A5 (CC1), R2.1
/CC2: J5.B5 (CC2), R3.1
/DATA_BUF: R10.1, U4.4
/DATA_IN: R9.1, U1.19 (IO14), U4.2
/DATA_OUT: J2.2, R10.2
/EN: C11.1, J6.2, R4.2, U1.8 (EN)
/IO18: J7.2, U1.24 (IO18)
/LED_A: D5.2 (A), R8.2
/Q1_G: D4.2 (A), Q1.4 (G), R1.1
/STATUS_LED: D5.1 (K), R6.2, U1.22 (IO8)
/SW_NODE: C5.2, L1.1, U2.5 (SW)
/SW_POS1: SW2.1, U1.27 (IO21)
/SW_POS2: SW2.2, U1.28 (IO22)
/SW_POS3: SW2.4, U1.29 (IO23)
/U0RXD: J6.5, U1.30 (RXD0)
/U0TXD: J6.6, U1.31 (TXD0)
/USB_DN: J5.A7 (D-), J5.B7 (D-), U1.17 (IO12), U5.3 (I/O2), U5.4 (I/O2)
/USB_DP: J5.A6 (D+), J5.B6 (D+), U1.18 (IO13), U5.1 (I/O1), U5.6 (I/O1)
/VBUS: C8.1, D2.2 (A), J5.A4 (VBUS), J5.A9 (VBUS), J5.B4 (VBUS), J5.B9 (VBUS), U5.5 (VBUS)
/VIN: J1.1, Q1.5 (D)
/VLED: C1.1, C12.1, D1.2 (A), D3.1 (A1), D4.1 (K), J2.1, Q1.1 (S), Q1.2 (S), Q1.3 (S), U3.1 (VI)
/V_SYS: C3.1, C4.1, D1.1 (K), D2.1 (K), U2.2 (EN), U2.3 (IN)
GND: C1.2, C3.2, C4.2, C6.2, C7.2, C8.2, C10.2, C11.2, C12.2, C13.2, D3.2 (A2), J1.2, J2.3, J5.A1 (GND), J5.A12 (GND), J5.B1 (GND), J5.B12 (GND), J5.S1 (SHIELD), J6.3, J7.3, R1.2, R2.2, R3.2, R9.2, SW1.2, SW2.3, U1.1 (GND), U1.2 (GND), U1.11 (GND), U1.14 (GND), U1.36 (GND), U1.37 (GND), U1.38 (GND), U1.39 (GND), U1.40 (GND), U1.41 (GND), U1.42 (GND), U1.43 (GND), U1.44 (GND), U1.45 (GND), U1.46 (GND), U1.47 (GND), U1.48 (GND), U1.49 (GND), U1.50 (GND), U1.51 (GND), U1.52 (GND), U1.53 (GND), U2.4 (GND), U3.3 (GND), U4.1, U4.3 (GND), U5.2 (GND)

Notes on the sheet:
NGUON VAO 5-12V / CHONG CAM NGUOC / TVS
NGUON 3.3V (buck AP63203)
5V CHO IC DICH MUC (chi co khi co nguon LED)
USB-C: NAP CODE / DEBUG (USB Serial/JTAG)
ESP32-C6-MINI-1 (Wi-Fi 6 / Thread / Zigbee)
DICH MUC 3.3V -> 5V + NGO RA WS2812
MO RONG: 1 GPIO TU DO (J7)
NUT / LED / CONG TAC 3 NAC / PAD NAP
SW1 (GPIO9 = BOOT): bam nhanh = bat/tat hoac vao che do ket noi; giu >5 s = factory reset. Giu SW1 trong luc cap nguon = vao che do nap ROM.
SW2 = C&K PCM13SMTR, chan 3 la chan chung (noi GND). Nac 1 noi 1-3, nac 2 noi 2-3, nac 3 noi 3-4. Firmware: IO21/IO22/IO23 la input, bat pull-up noi; chan nao doc 0 -> chia day LED thanh 1/2/3 doan, moi doan la mot endpoint Matter. Khong chan nao doc 0 (dang gat giua 2 nac) -> giu gia tri cu.
Q1 chong cam nguoc. Dong toi da 5 A. TVS D3 kep xung qua ap. Khong co cau chi: dung nguon co bao ve ngan mach.
DATA 5V: WS2812B (5V) va WS2811 (12V) deu nhan muc 5V.
IO18: GPIO thuong, pull-up yeu chi trong luc reset. Muc 3,3 V, khong chiu 5 V.
IO0-IO7, IO15, IO19, IO20: de trong. Anten module nho ra ngoai mep board (khong de dong).

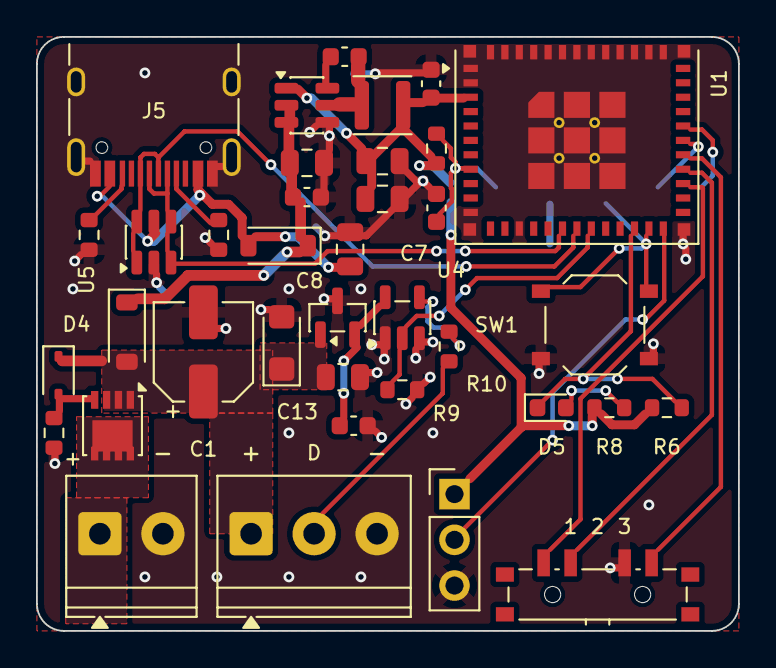
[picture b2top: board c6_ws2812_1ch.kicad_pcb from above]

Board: 2 copper layers, 39.0 x 33.0 mm, 38 parts (1 on the bottom side), 27 nets.

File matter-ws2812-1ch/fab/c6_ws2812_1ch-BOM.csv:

Comment,Designator,Footprint,Quantity,MPN / note,LCSC Part #,Mount
VIN 5-12V,J1,"TerminalBlock_Phoenix_PT-1,5-2-3.5-H_1x02_P3.50mm_Horizontal",1,"Terminal block 2P 3.5mm (Phoenix PT 1,5/2-3,5-H / KF350-3.5-2P)",,THT
SiSS27DN,Q1,Vishay_PowerPAK_1212-8_Single,1,SiSS27DN-T1-GE3,,SMD
BZT52C15S,D4,D_SOD-323,1,BZT52C15S,,SMD
10k,"R1,R4,R6,R9",R_0603_1608Metric,4,0603 1% 10k,C25804,SMD
SMF15A,D3,D_SMF,1,SMF15A,,SMD
47uF 25V,C1,CP_Elec_5x5.4,1,47uF 25V 5x5.4 SMD electrolytic,,SMD
B5819W,"D1,D2",D_SOD-123,2,B5819W,C8598,SMD
10uF 25V,C3,C_0805_2012Metric,1,MLCC 10uF 25V,,SMD
100nF 50V,C4,C_0603_1608Metric,1,MLCC 100nF 50V,C14663,SMD
AP63203WU-7,U2,TSOT-23-6,1,AP63203WU-7,C780769,SMD
100nF,"C5,C10",C_0603_1608Metric,2,MLCC 100nF,C14663,SMD
3.9uH,L1,L_Sunlord_SWPA3015S,1,SWPA3015S3R9MT,,SMD
22uF 10V,"C6,C7",C_0805_2012Metric,2,MLCC 22uF 10V,,SMD
USB-C,J5,USB_C_Receptacle_HRO_TYPE-C-31-M-12_EdgeSilk,1,HRO TYPE-C-31-M-12,C165948,SMD
5.1k,"R2,R3",R_0603_1608Metric,2,0603 1% 5.1k,C23186,SMD
USBLC6-2SC6,U5,SOT-23-6,1,USBLC6-2SC6,C7519,SMD
4.7uF 25V,C8,C_0805_2012Metric,1,MLCC 4.7uF 25V,,SMD
ESP32-C6-MINI-1-N4,U1,ESP32-C6-MINI-1_ThermalVias,1,ESP32-C6-MINI-1-N4,,SMD
1uF 10V,C11,C_0603_1608Metric,1,MLCC 1uF 10V,,SMD
LINK / RESET,SW1,SW_Push_1P1T_XKB_TS-1187A,1,XKB TS-1187A-B-A-B,C318884,SMD
1k,R8,R_0603_1608Metric,1,0603 1% 1k,C21190,SMD
Green,D5,LED_0603_1608Metric,1,LED 0603 green,C72043,SMD
ENDPOINTS 1/2/3,SW2,SW_SP3T_PCM13_EdgeSilk,1,"C&K PCM13SMTR (SP3T, pos.1 = 1-3, pos.2 = 2-3, pos.3 = 3-4)",C221842,SMD
AP7381-50SA-7,U3,SOT-23,1,AP7381-50SA-7,,SMD
1uF 50V,C12,C_0805_2012Metric,1,MLCC 1uF 50V,,SMD
2.2uF 10V,C13,C_0603_1608Metric,1,MLCC 2.2uF 10V,,SMD
74AHCT1G125,U4,SOT-23-5,1,SN74AHCT1G125DBVR,,SMD
100,R10,R_0603_1608Metric,1,0603 1% 100,C22775,SMD
LED V+ D GND,J2,"TerminalBlock_Phoenix_PT-1,5-3-3.5-H_1x03_P3.50mm_Horizontal",1,"Terminal block 3P 3.5mm (Phoenix PT 1,5/3-3,5-H / KF350-3.5-3P)",,THT
GPIO,J7,PinHeader_1x03_P2.54mm_Vertical,1,Pin header 1x3 2.54mm,,THT
